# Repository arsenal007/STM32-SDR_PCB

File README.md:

# STM32-SDR_PCB
KiCAD PCB Project of STM32 SDR, processor board

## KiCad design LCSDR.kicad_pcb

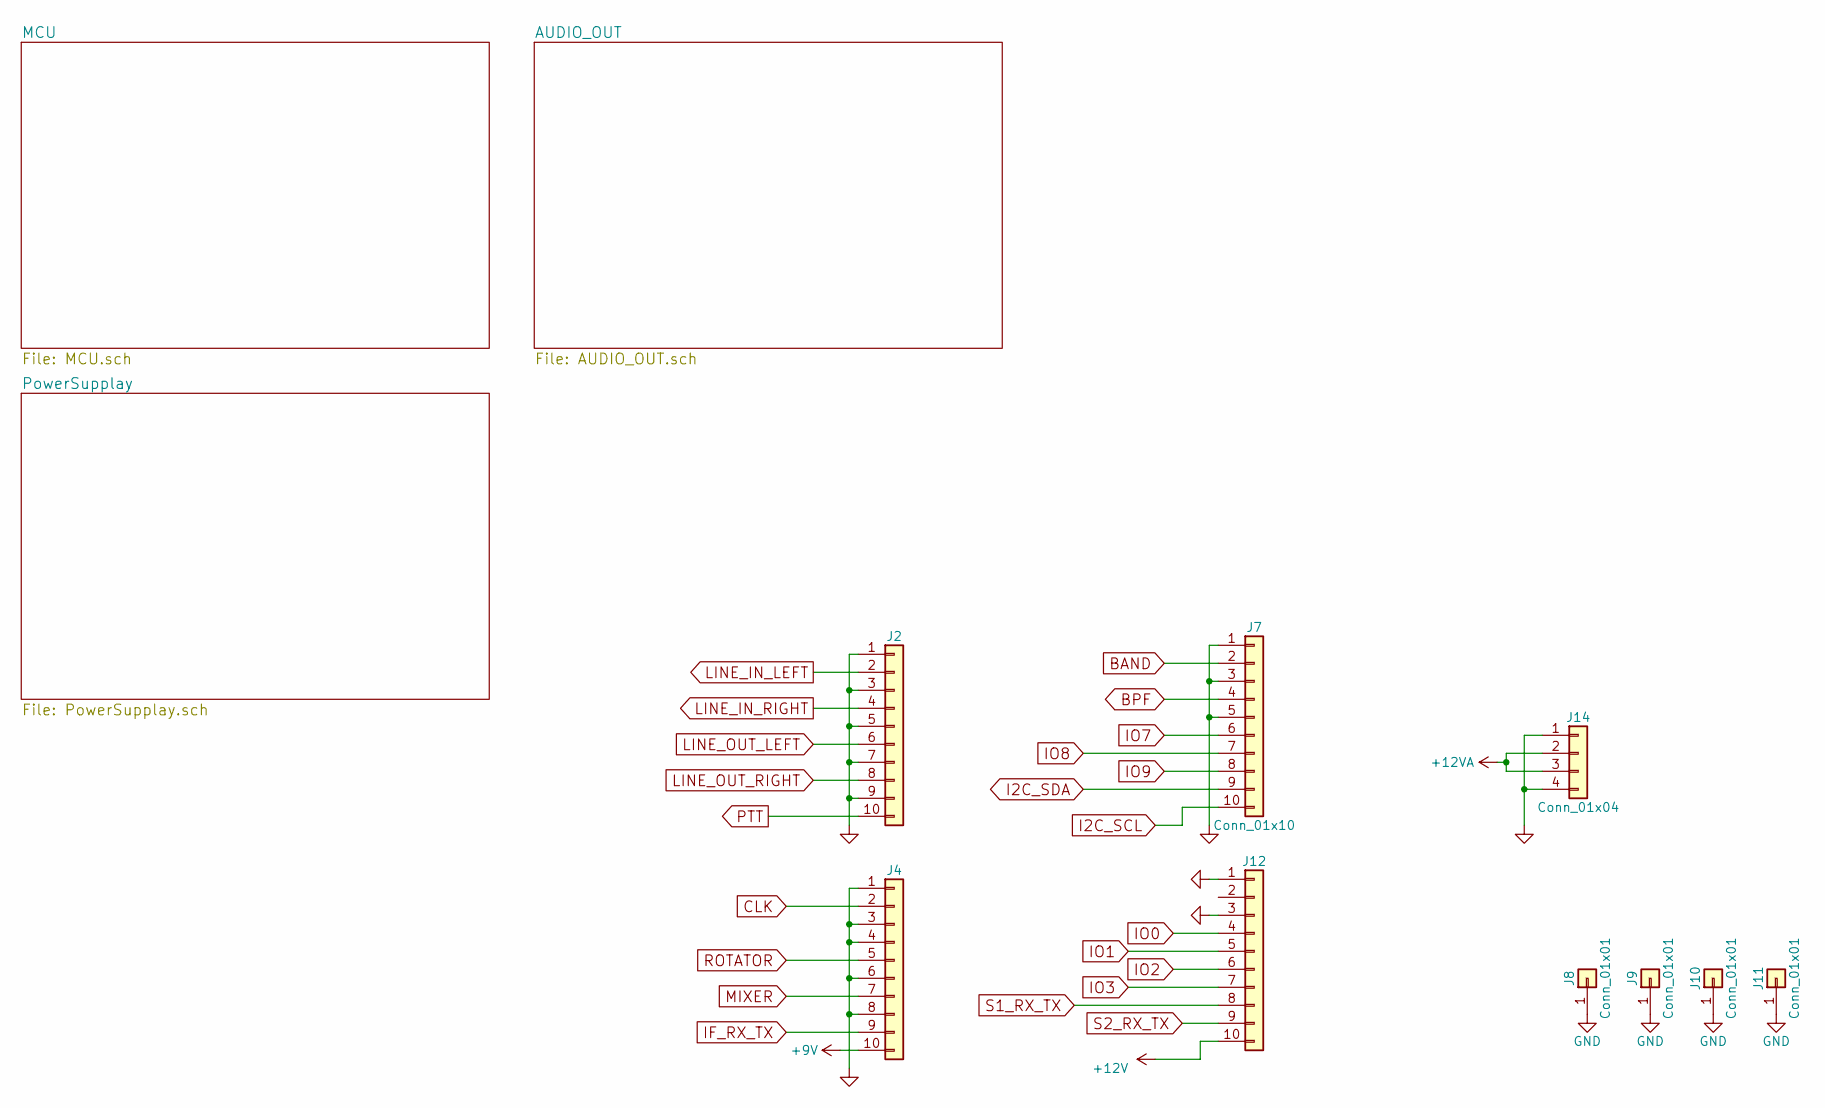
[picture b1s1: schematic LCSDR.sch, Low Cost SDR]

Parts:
J2, J4, J7, J12: Conn_01x10; Pin_Header_Straight_1x10_Pitch2.54mm
J8, J9, J10, J11: Conn_01x01; MountingHole_3.2mm_M3_DIN965_Pad
J14: Conn_01x04; Pin_Header_Straight_1x04_Pitch2.54mm

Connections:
+9V: J4.10; also elsewhere on the board
+12V: J12.10; also elsewhere on the board
+12VA: J14.2, J14.3; also elsewhere on the board
BAND: J7.2; also elsewhere on the board
CLK: J4.2; also elsewhere on the board
GND: J2.1, J2.3, J2.5, J2.7, J2.9, J4.1, J4.3, J4.4, J4.6, J4.8, J7.1, J7.3, J7.5, J8.1, J9.1, J10.1, J11.1, J12.1, J12.3, J14.1, J14.4; also elsewhere on the board
I2C_SCL: J7.10; also elsewhere on the board
I2C_SDA: J7.9; also elsewhere on the board
IF_RX_TX: J4.9; also elsewhere on the board
IO0: J12.4; also elsewhere on the board
IO1: J12.5; also elsewhere on the board
IO2: J12.6; also elsewhere on the board
IO3: J12.7; also elsewhere on the board
IO7: J7.6; also elsewhere on the board
IO8: J7.7; also elsewhere on the board
IO9: J7.8; also elsewhere on the board
LINE_IN_LEFT: J2.2; also elsewhere on the board
LINE_IN_RIGHT: J2.4; also elsewhere on the board
LINE_OUT_LEFT: J2.6; also elsewhere on the board
LINE_OUT_RIGHT: J2.8; also elsewhere on the board
MIXER: J4.7; also elsewhere on the board
PTT: J2.10; also elsewhere on the board
ROTATOR: J4.5; also elsewhere on the board
S1_RX_TX: J12.8; also elsewhere on the board
S2_RX_TX: J12.9; also elsewhere on the board

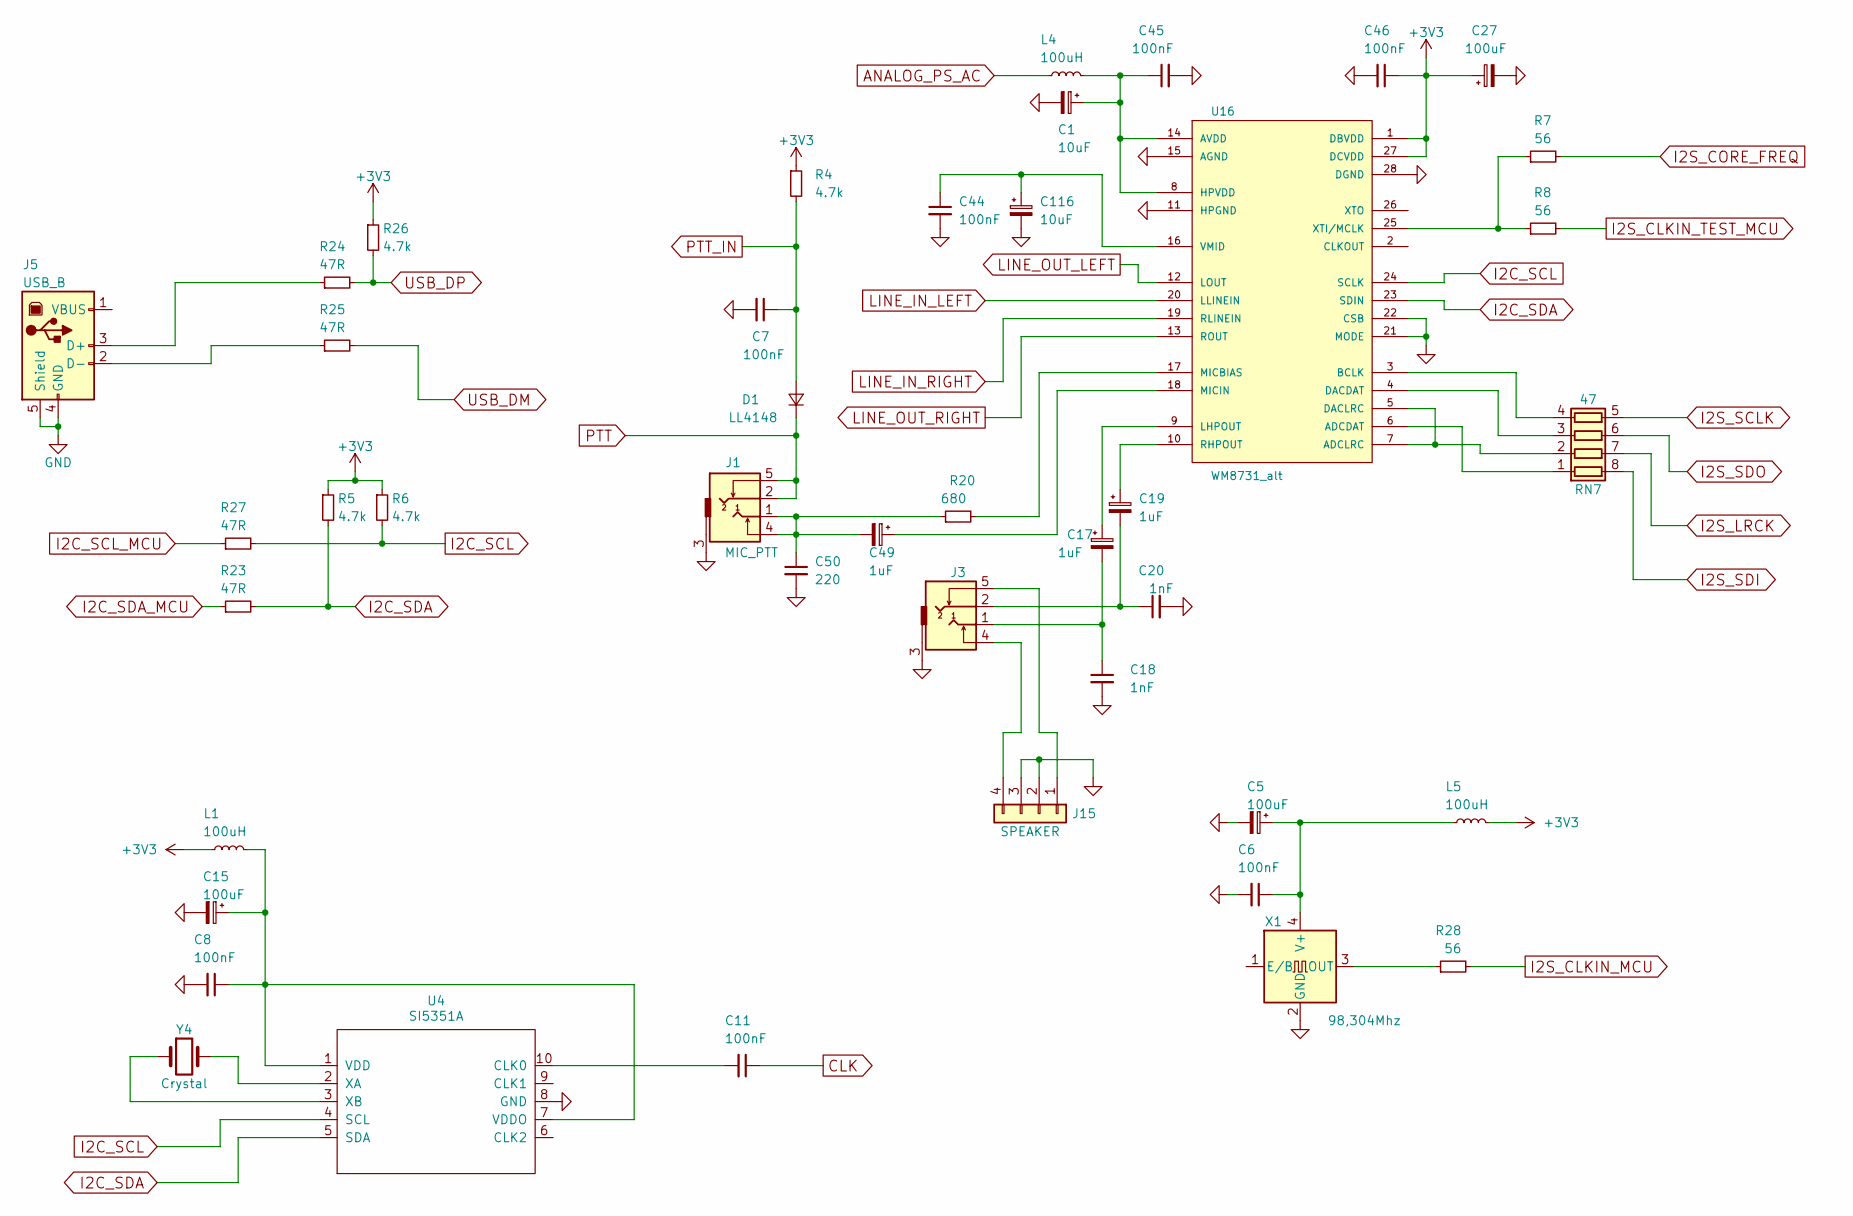
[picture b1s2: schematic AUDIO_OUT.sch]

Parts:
C1, C116: 10uF; CP_Radial_D5.0mm_P2.00mm
C5, C15, C27: 100uF; CP_Radial_D6.3mm_P2.50mm
C6, C7, C8, C11, C44, C45, C46: 100nF; C_1206_0603
C17, C19, C49: 1uF; CP_Radial_D4.0mm_P2.00mm
C18, C20: 1nF; C_1206_0603
C50: 220; C_1206_0603
D1: LL4148; D_DO-35_SOD27_P10.16mm_Horizontal
J1: MIC_PTT; audio_jack_3_5mm_PJ307
J3: Audio-Jack-3_2Switches; audio_jack_3_5mm_PJ307
J5: USB_B
J15: SPEAKER; Pin_Header_Straight_1x04_Pitch2.54mm
L1, L4, L5: 100uH; Choke_Horizontal_RM10mm
R4, R5, R6, R26: 4.7k; R_Axial_DIN0204_L3.6mm_D1.6mm_P7.62mm_Horizontal
R7, R8, R28: 56; R_Axial_DIN0204_L3.6mm_D1.6mm_P7.62mm_Horizontal
R20: 680; R_1206_0603
R23, R24, R25, R27: 47R; R_Axial_DIN0204_L3.6mm_D1.6mm_P7.62mm_Horizontal
RN7: 47; R_Array_Convex_4x0603
U4: SI5351A; MSOP-10_3x3mm_Pitch0.5mm
U16: WM8731_alt; SSOP-28_5.3x10.2mm_Pitch0.65mm
X1: 98,304Mhz; Oscillator_SMD_IQD_IQXO70-4pin_7.5x5.0mm
Y4: Crystal; Crystal_HC49-U_Vertical

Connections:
+3V3: C27.1, C46.1, L1.1, L5.2, R4.1, R5.1, R6.1, R26.1, U16.1 (DBVDD), U16.27 (DCVDD); also elsewhere on the board
ANALOG_PS_AC: L4.1; also elsewhere on the board
CLK: C11.1; also elsewhere on the board
GND: C1.2, C5.2, C6.2, C7.2, C8.2, C15.2, C18.2, C20.2, C27.2, C44.2, C45.2, C46.2, C50.2, C116.2, J1.3, J3.3, J5.4 (GND), J5.5 (Shield), J15.2, J15.3, U4.8 (GND), U16.11 (HPGND), U16.15 (AGND), U16.21 (MODE), U16.22 (CSB), U16.28 (DGND), X1.2 (GND); also elsewhere on the board
I2C_SCL: R6.2, R27.2, U4.4 (SCL), U16.24 (SCLK); also elsewhere on the board
I2C_SCL_MCU: R27.1; also elsewhere on the board
I2C_SDA: R5.2, R23.2, U4.5 (SDA), U16.23 (SDIN); also elsewhere on the board
I2C_SDA_MCU: R23.1; also elsewhere on the board
I2S_CLKIN_MCU: R28.2; also elsewhere on the board
I2S_CLKIN_TEST_MCU: R8.2; also elsewhere on the board
I2S_CORE_FREQ: R7.2; also elsewhere on the board
I2S_LRCK: RN7.7 (R2.2); also elsewhere on the board
I2S_SCLK: RN7.5 (R4.2); also elsewhere on the board
I2S_SDI: RN7.8 (R1.2); also elsewhere on the board
I2S_SDO: RN7.6 (R3.2); also elsewhere on the board
LINE_IN_LEFT: U16.20 (LLINEIN); also elsewhere on the board
LINE_IN_RIGHT: U16.19 (RLINEIN); also elsewhere on the board
LINE_OUT_LEFT: U16.12 (LOUT); also elsewhere on the board
LINE_OUT_RIGHT: U16.13 (ROUT); also elsewhere on the board
unnamed: C1.1, C45.1, L4.2, U16.8 (HPVDD), U16.14 (AVDD)
unnamed: C5.1, C6.1, L5.1, X1.4 (V+)
unnamed: C11.2, U4.10 (CLK0)
unnamed: C8.1, C15.1, L1.2, U4.1 (VDD), U4.7 (VDDO)
unnamed: C17.1, U16.9 (LHPOUT)
unnamed: C17.2, C18.1, J3.1
unnamed: C19.1, U16.10 (RHPOUT)
unnamed: C19.2, C20.1, J3.2
unnamed: C49.1, U16.18 (MICIN)
unnamed: C49.2, C50.1, J1.1, J1.4, R20.1
unnamed: C44.1, C116.1, U16.16 (VMID)
unnamed: J5.2 (D-), R25.1
unnamed: J5.3 (D+), R24.1
unnamed: J3.5, J15.1
unnamed: J3.4, J15.4
unnamed: R7.1, R8.1, U16.25 (XTI/MCLK)
unnamed: R20.2, U16.17 (MICBIAS)
unnamed: R28.1, X1.3 (OUT)
unnamed: RN7.1 (R1.1), U16.6 (ADCDAT)
unnamed: RN7.2 (R2.1), U16.5 (DACLRC), U16.7 (ADCLRC)
unnamed: RN7.3 (R3.1), U16.4 (DACDAT)
unnamed: RN7.4 (R4.1), U16.3 (BCLK)
unnamed: U4.2 (XA), Y4.2
unnamed: U4.3 (XB), Y4.1
PTT: D1.1 (K), J1.2, J1.5; also elsewhere on the board
PTT_IN: C7.1, D1.2 (A), R4.2; also elsewhere on the board
USB_DM: R25.2; also elsewhere on the board
USB_DP: R24.2, R26.2; also elsewhere on the board

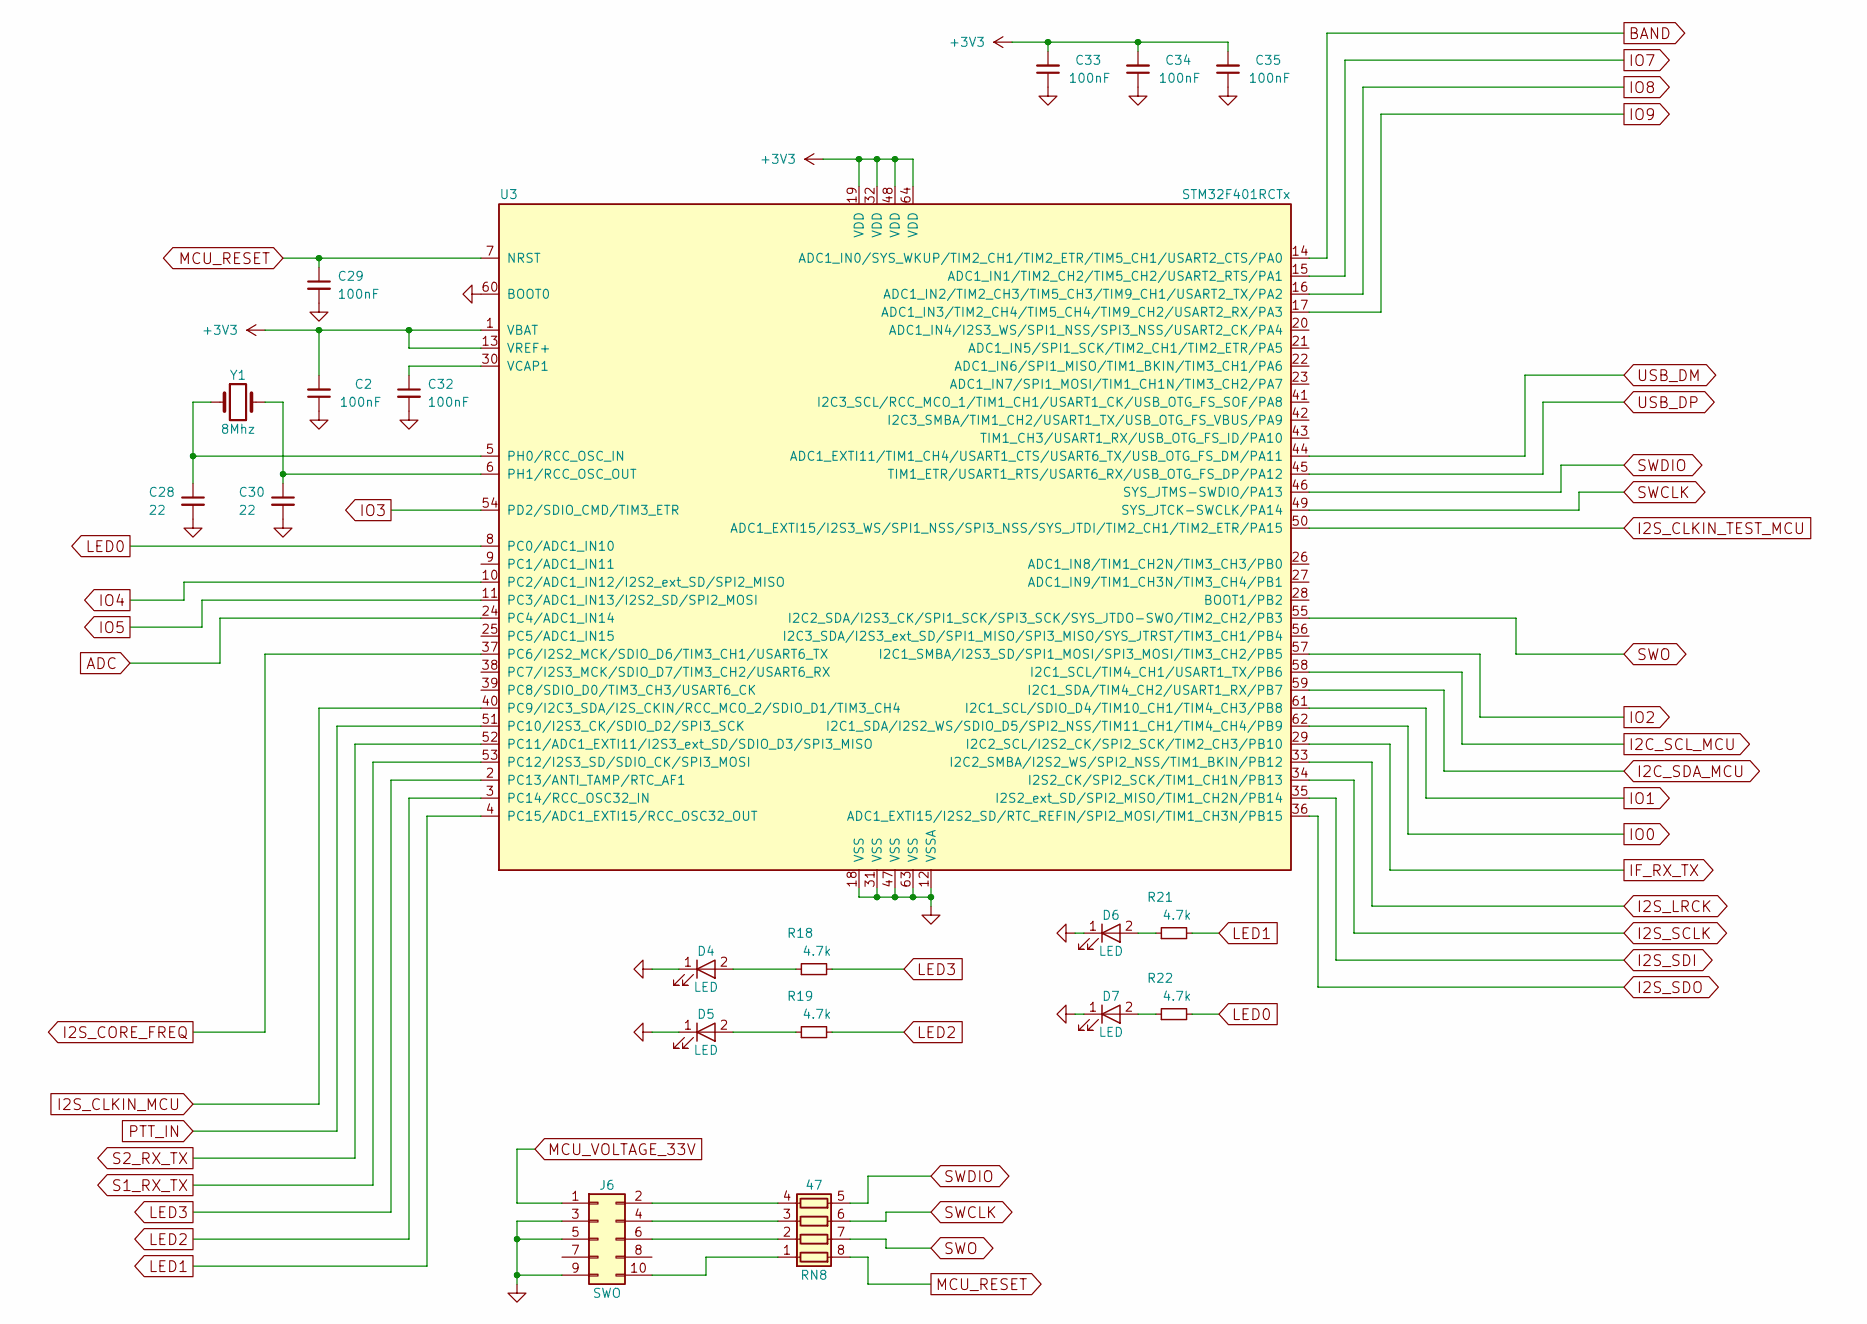
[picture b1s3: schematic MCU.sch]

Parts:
C2, C29, C32, C33, C34, C35: 100nF; C_1206_0603
C28, C30: 22; C_1206_0603
D4, D5, D6, D7: LED; LED_D5.0mm_FlatTop
J6: SWO; Pin_Header_Straight_2x05_Pitch2.54mm
R18, R19, R21, R22: 4.7k; R_Axial_DIN0204_L3.6mm_D1.6mm_P7.62mm_Horizontal
RN8: 47; R_Array_Convex_4x0603
U3: STM32F401RCTx; TQFP-64_10x10mm_Pitch0.5mm
Y1: 8Mhz; Crystal_HC49-U_Vertical

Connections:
+3V3: C2.2, C33.2, C34.2, C35.2, U3.1 (VBAT), U3.13 (VREF+), U3.19 (VDD), U3.32 (VDD), U3.48 (VDD), U3.64 (VDD); also elsewhere on the board
BAND: U3.14 (ADC1_IN0/SYS_WKUP/TIM2_CH1/TIM2_ETR/TIM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); also elsewhere on the board
GND: C2.1, C28.2, C29.2, C30.2, C32.2, C33.1, C34.1, C35.1, D4.1 (K), D5.1 (K), D6.1 (K), D7.1 (K), J6.3, J6.5, J6.9, U3.12 (VSSA), U3.18 (VSS), U3.31 (VSS), U3.47 (VSS), U3.60 (BOOT0), U3.63 (VSS); also elsewhere on the board
I2C_SCL_MCU: U3.58 (I2C1_SCL/TIM4_CH1/USART1_TX/PB6); also elsewhere on the board
I2C_SDA_MCU: U3.59 (I2C1_SDA/TIM4_CH2/USART1_RX/PB7); also elsewhere on the board
I2S_CLKIN_MCU: U3.40 (PC9/I2C3_SDA/I2S_CKIN/RCC_MCO_2/SDIO_D1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); also elsewhere on the board
I2S_CLKIN_TEST_MCU: U3.50 (ADC1_EXTI15/I2S3_WS/SPI1_NSS/SPI3_NSS/S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); also elsewhere on the board
I2S_CORE_FREQ: U3.37 (PC6/I2S2_MCK/SDIO_D6/TIM3_CH1/USART6_TX); also elsewhere on the board
I2S_LRCK: U3.33 (I2C2_SMBA/I2S2_WS/SPI2_NSS/TIM1_BKIN/PB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); also elsewhere on the board
I2S_SCLK: U3.34 (I2S2_CK/SPI2_SCK/TIM1_CH1N/PB13); also elsewhere on the board
I2S_SDI: U3.35 (I2S2_ext_SD/SPI2_MISO/TIM1_CH2N/PB14); also elsewhere on the board
I2S_SDO: U3.36 (ADC1_EXTI15/I2S2_SD/RTC_REFIN/SPI2_MOSI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); also elsewhere on the board
IF_RX_TX: U3.29 (I2C2_SCL/I2S2_CK/SPI2_SCK/TIM2_CH3/PB10); also elsewhere on the board
IO0: U3.62 (I2C1_SDA/I2S2_WS/SDIO_D5/SPI2_NSS/TIM11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); also elsewhere on the board
IO1: U3.61 (I2C1_SCL/SDIO_D4/TIM10_CH1/TIM4_CH3/PB8); also elsewhere on the board
IO2: U3.57 (I2C1_SMBA/I2S3_SD/SPI1_MOSI/SPI3_MOSI/T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); also elsewhere on the board
IO3: U3.54 (PD2/SDIO_CMD/TIM3_ETR); also elsewhere on the board
IO7: U3.15 (ADC1_IN1/TIM2_CH2/TIM5_CH2/USART2_RTS/P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); also elsewhere on the board
IO8: U3.16 (ADC1_IN2/TIM2_CH3/TIM5_CH3/TIM9_CH1/USA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); also elsewhere on the board
IO9: U3.17 (ADC1_IN3/TIM2_CH4/TIM5_CH4/TIM9_CH2/USA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); also elsewhere on the board
LED0: R22.2, U3.8 (PC0/ADC1_IN10)
LED1: R21.2, U3.4 (PC15/ADC1_EXTI15/RCC_OSC32_OUT)
LED2: R19.2, U3.3 (PC14/RCC_OSC32_IN)
LED3: R18.2, U3.2 (PC13/ANTI_TAMP/RTC_AF1)
MCU_RESET: C29.1, RN8.8 (R1.2), U3.7 (NRST)
unnamed: C28.1, U3.5 (PH0/RCC_OSC_IN), Y1.1
unnamed: C30.1, U3.6 (PH1/RCC_OSC_OUT), Y1.2
unnamed: C32.1, U3.30 (VCAP1)
unnamed: D4.2 (A), R18.1
unnamed: D5.2 (A), R19.1
unnamed: D6.2 (A), R21.1
unnamed: D7.2 (A), R22.1
unnamed: J6.2, RN8.4 (R4.1)
unnamed: J6.4, RN8.3 (R3.1)
unnamed: J6.6, RN8.2 (R2.1)
unnamed: J6.10, RN8.1 (R1.1)
PTT_IN: U3.51 (PC10/I2S3_CK/SDIO_D2/SPI3_SCK); also elsewhere on the board
S1_RX_TX: U3.53 (PC12/I2S3_SD/SDIO_CK/SPI3_MOSI); also elsewhere on the board
S2_RX_TX: U3.52 (PC11/ADC1_EXTI11/I2S3_ext_SD/SDIO_D3/SP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); also elsewhere on the board
SWCLK: RN8.6 (R3.2), U3.49 (SYS_JTCK-SWCLK/PA14)
SWDIO: RN8.5 (R4.2), U3.46 (SYS_JTMS-SWDIO/PA13)
SWO: RN8.7 (R2.2), U3.55 (I2C2_SDA/I2S3_CK/SPI1_SCK/SPI3_SCK/SYS_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)
USB_DM: U3.44 (ADC1_EXTI11/TIM1_CH4/USART1_CTS/USART6_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); also elsewhere on the board
USB_DP: U3.45 (TIM1_ETR/USART1_RTS/USART6_RX/USB_OTG_F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); also elsewhere on the board

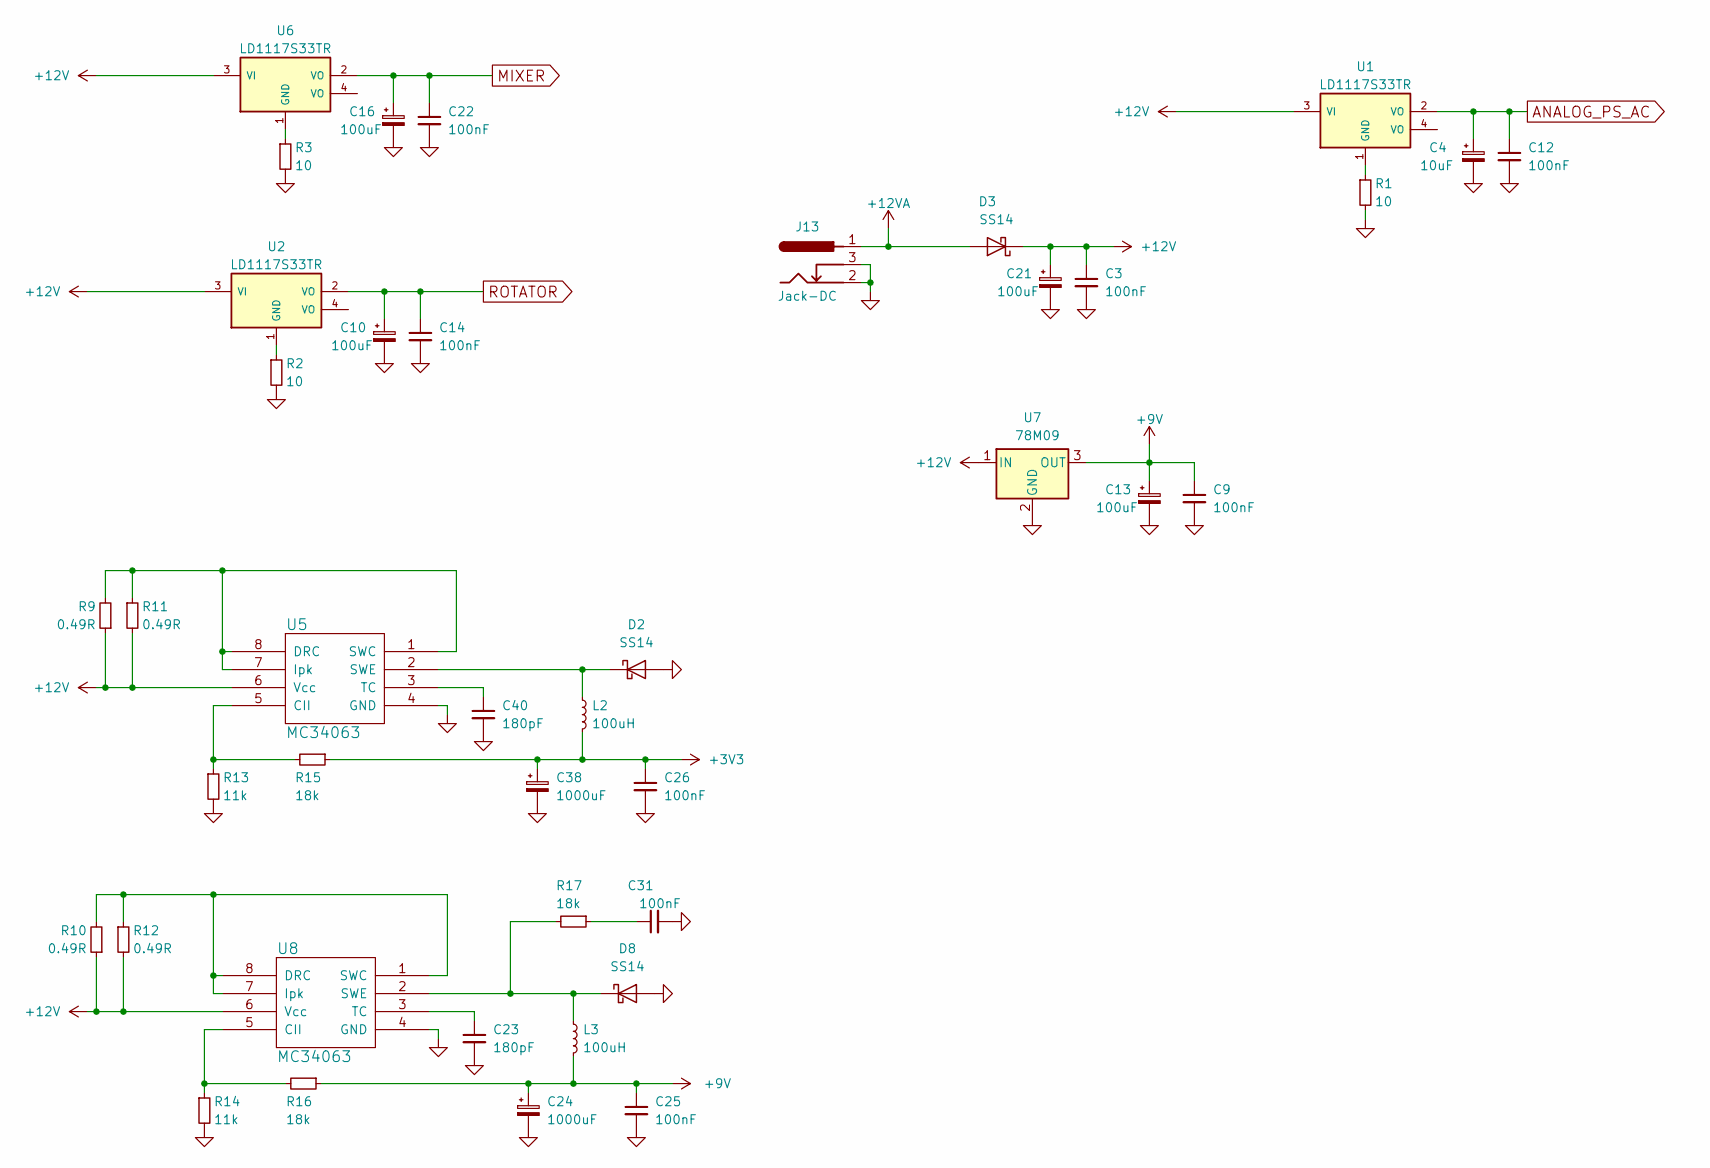
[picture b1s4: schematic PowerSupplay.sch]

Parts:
C3, C9, C12, C14, C22, C25, C26, C31: 100nF; C_1206_0603
C4: 10uF; CP_Radial_D5.0mm_P2.00mm
C10, C13, C16, C21: 100uF; CP_Radial_D6.3mm_P2.50mm
C23, C40: 180pF; C_1206_0603
C24, C38: 1000uF; CP_Radial_D10.0mm_P5.00mm
D2, D3, D8: SS14; D_SMA_Handsoldering
J13: Jack-DC; BARREL_JACK
L2, L3: 100uH; Choke_Toroid_6,5x13mm_Vertical
R1, R2, R3: 10; R_1206_0603
R9, R10, R11, R12: 0.49R; R_Axial_DIN0204_L3.6mm_D1.6mm_P7.62mm_Horizontal
R13, R14: 11k; R_1206_0603
R15, R16, R17: 18k; R_1206_0603
U1, U2, U6: LD1117S33TR; SOT-223
U5, U8: MC34063; SOIC-8_3.9x4.9mm_Pitch1.27mm
U7: 78M09; TO-252-2_Rectifier

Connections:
+3V3: C26.1, C38.1, L2.2, R15.1; also elsewhere on the board
+9V: C9.1, C13.1, C24.1, C25.1, L3.2, R16.1, U7.3 (OUT); also elsewhere on the board
+12V: C3.1, C21.1, D3.1 (K), R9.1, R10.1, R11.2, R12.2, U1.3 (VI), U2.3 (VI), U5.6 (Vcc), U6.3 (VI), U7.1 (IN), U8.6 (Vcc); also elsewhere on the board
+12VA: D3.2 (A), J13.1; also elsewhere on the board
ANALOG_PS_AC: C4.1, C12.1, U1.2 (VO); also elsewhere on the board
GND: C3.2, C4.2, C9.2, C10.2, C12.2, C13.2, C14.2, C16.2, C21.2, C22.2, C23.2, C24.2, C25.2, C26.2, C31.2, C38.2, C40.2, D2.2 (A), D8.2 (A), J13.2, J13.3, R1.2, R2.2, R3.2, R13.2, R14.2, U5.4 (GND), U7.2 (GND), U8.4 (GND); also elsewhere on the board
MIXER: C16.1, C22.1, U6.2 (VO); also elsewhere on the board
unnamed: C23.1, U8.3 (TC)
unnamed: C31.1, R17.1
unnamed: C40.1, U5.3 (TC)
unnamed: D2.1 (K), L2.1, U5.2 (SWE)
unnamed: D8.1 (K), L3.1, R17.2, U8.2 (SWE)
unnamed: R1.1, U1.1 (GND)
unnamed: R2.1, U2.1 (GND)
unnamed: R3.1, U6.1 (GND)
unnamed: R10.2, R12.1, U8.1 (SWC), U8.7 (Ipk), U8.8 (DRC)
unnamed: R9.2, R11.1, U5.1 (SWC), U5.7 (Ipk), U5.8 (DRC)
unnamed: R13.1, R15.2, U5.5 (CII)
unnamed: R14.1, R16.2, U8.5 (CII)
ROTATOR: C10.1, C14.1, U2.2 (VO); also elsewhere on the board

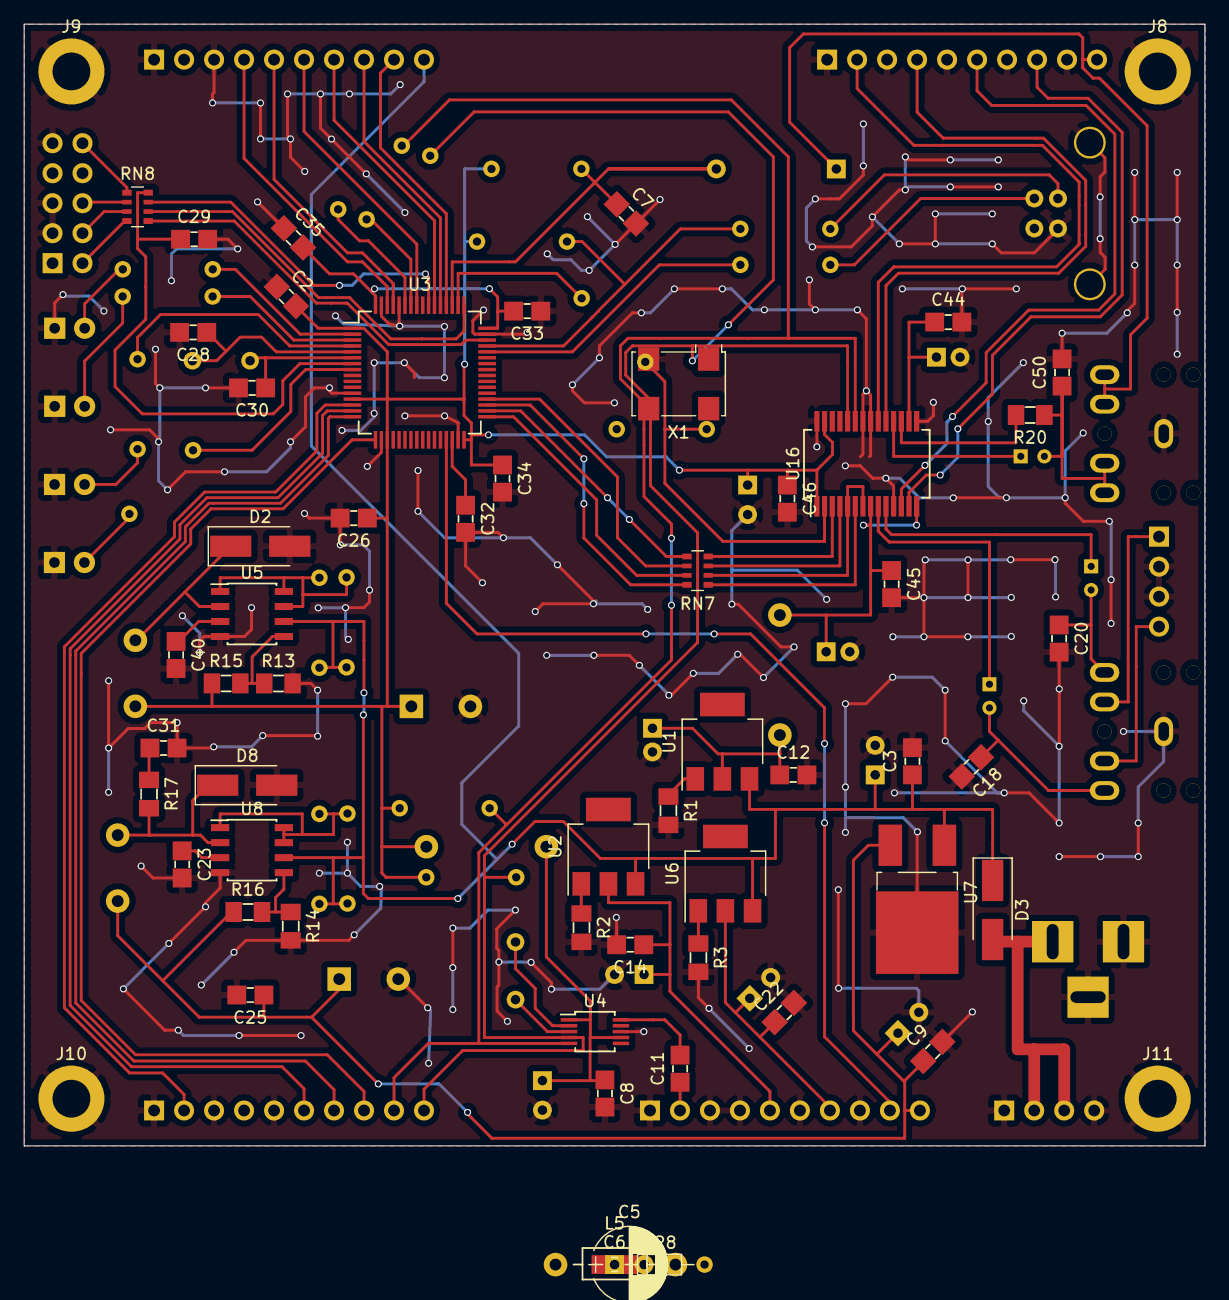
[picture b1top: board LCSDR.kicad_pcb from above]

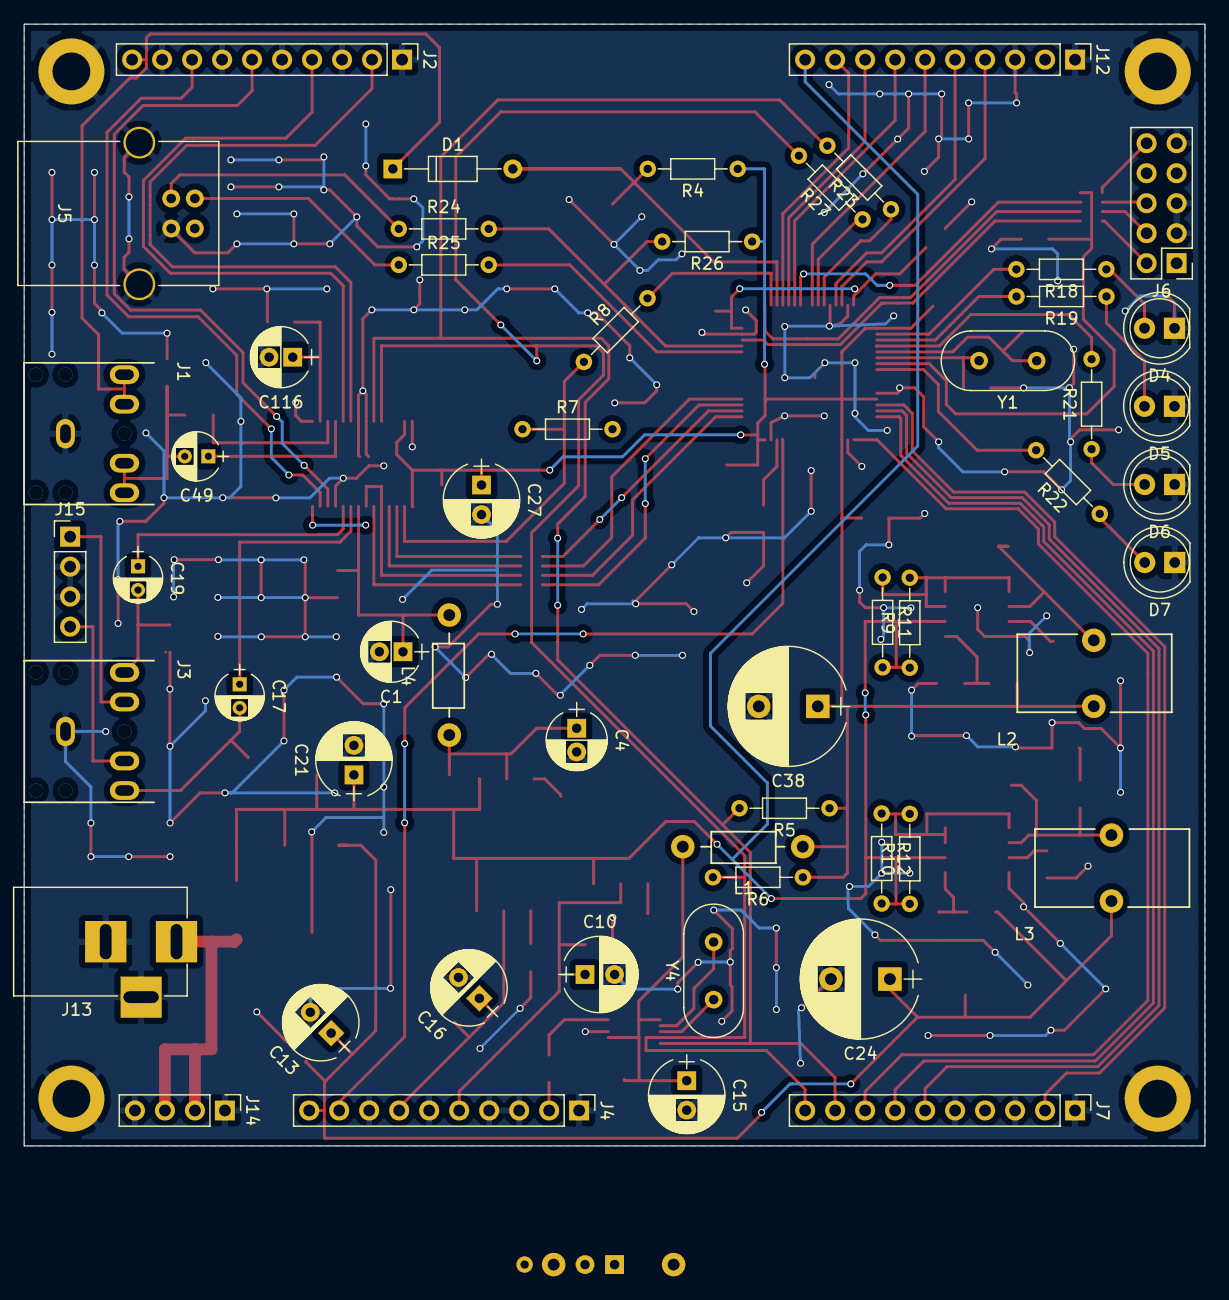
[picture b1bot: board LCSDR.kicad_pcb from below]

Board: 2 copper layers, 100.0 x 95.0 mm, 113 parts (54 on the bottom side), 94 nets.
